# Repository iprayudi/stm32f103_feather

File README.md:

# stm32f103_feather
 Feather-compatible STM32F103 development board

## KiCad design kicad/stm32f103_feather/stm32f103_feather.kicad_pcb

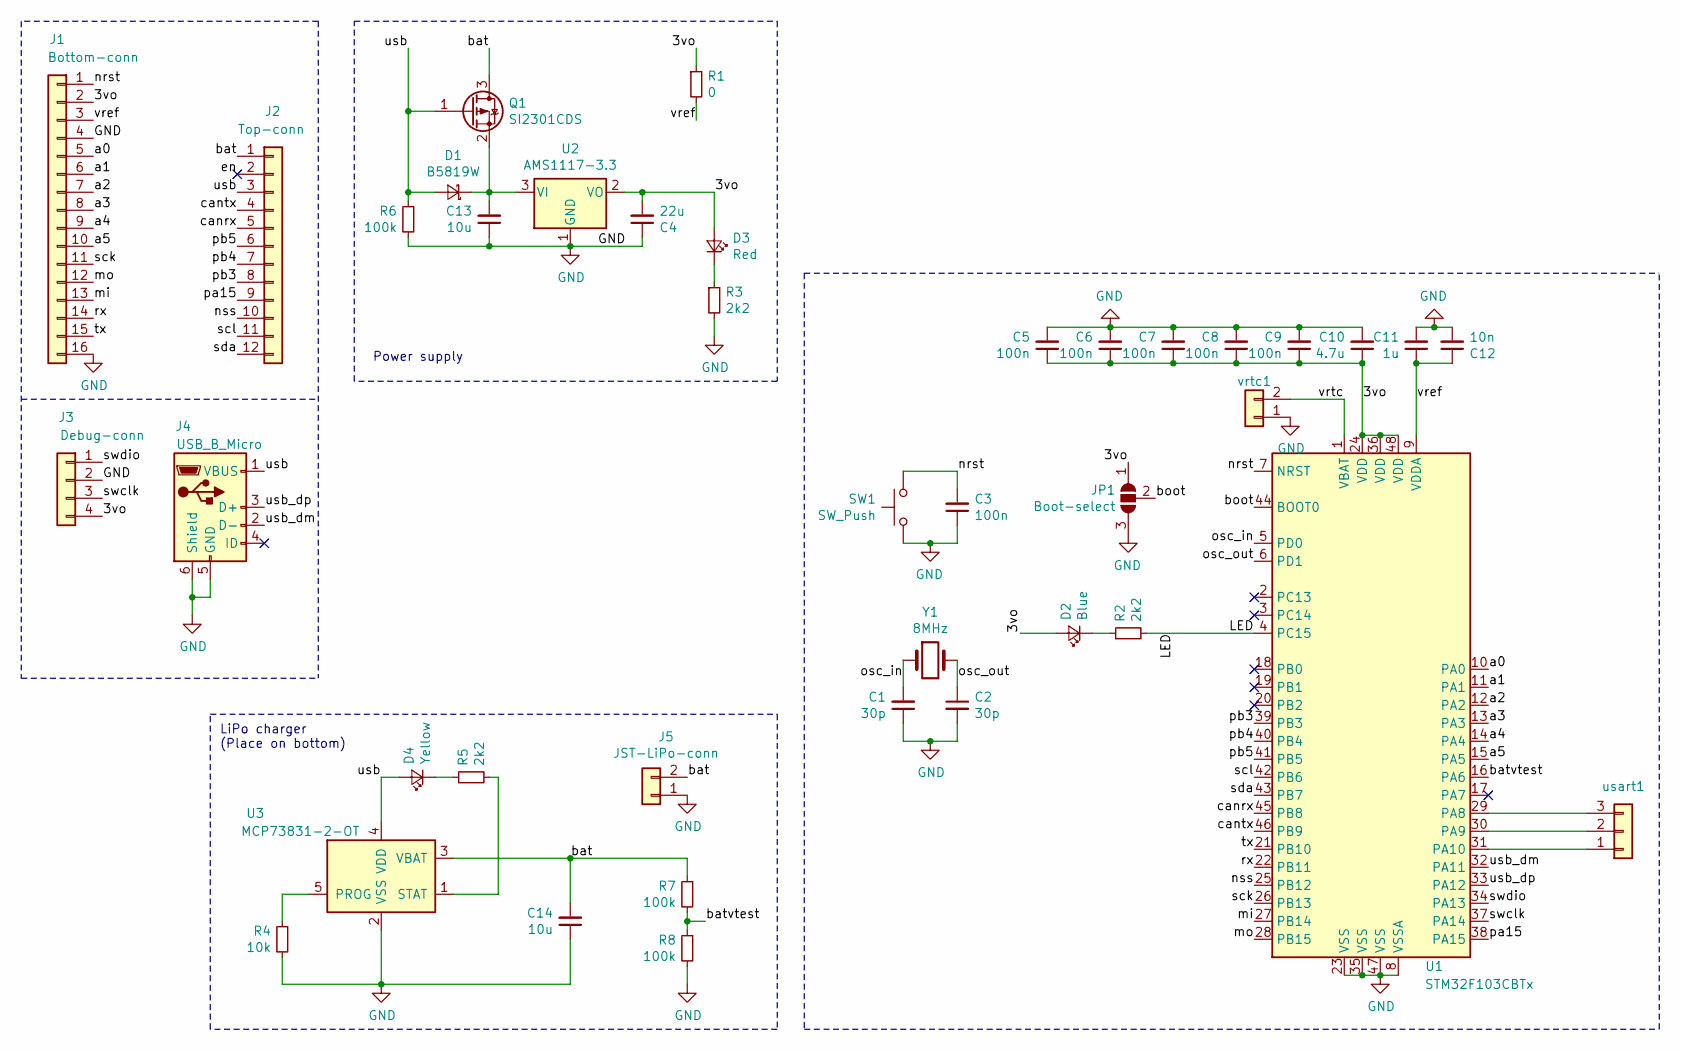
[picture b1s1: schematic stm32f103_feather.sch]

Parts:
C1, C2: 30p; C_0603_1608Metric_Pad1.05x0.95mm_HandSolder; LCSC C22397
C3, C5, C6, C7, C8, C9: 100n; C_0603_1608Metric_Pad1.05x0.95mm_HandSolder; LCSC C14663
C4: 22u; C_0603_1608Metric_Pad1.05x0.95mm_HandSolder; LCSC C59461
C10: 4.7u; C_0603_1608Metric_Pad1.05x0.95mm_HandSolder; LCSC C19666
C11: 1u; C_0805_2012Metric_Pad1.15x1.40mm_HandSolder; LCSC C15849
C12: 10n; C_0805_2012Metric_Pad1.15x1.40mm_HandSolder; LCSC C57112
C13: 10u; C_0603_1608Metric_Pad1.05x0.95mm_HandSolder; LCSC C19702
C14: 10u; C_0805_2012Metric_Pad1.15x1.40mm_HandSolder; LCSC C19702
D1: B5819W; D_SOD-123; LCSC C8598
D2: Blue; D_0603_1608Metric_Pad1.05x0.95mm_HandSolder; LCSC C72041
D3: Red; D_0603_1608Metric_Pad1.05x0.95mm_HandSolder; LCSC C2286
D4: Yellow; D_0805_2012Metric_Pad1.15x1.40mm_HandSolder; LCSC C72038
J1: Bottom-conn; PinSocket_1x16_P2.54mm_Vertical
J2: Top-conn; PinSocket_1x12_P2.54mm_Vertical
J3: Debug-conn; PinHeader_1x04_P2.54mm_Vertical
J4: USB_B_Micro; USB_Micro-B_Wuerth_629105150521
J5: JST-LiPo-conn; JST_PH_S2B-PH-SM4-TB_1x02-1MP_P2.00mm_Horizontal
JP1: Boot-select; PinHeader_1x03_P2.54mm_Vertical
Q1: SI2301CDS; SOT-23; LCSC C10487
R1: 0; R_0603_1608Metric_Pad1.05x0.95mm_HandSolder; LCSC C21189
R2, R3: 2k2; R_0603_1608Metric_Pad1.05x0.95mm_HandSolder; LCSC C4190
R4: 10k; R_0805_2012Metric_Pad1.15x1.40mm_HandSolder; LCSC C25804
R5: 2k2; R_0805_2012Metric_Pad1.15x1.40mm_HandSolder; LCSC C4190
R6: 100k; R_0603_1608Metric_Pad1.05x0.95mm_HandSolder; LCSC C25803
R7, R8: 100k; R_0805_2012Metric_Pad1.15x1.40mm_HandSolder; LCSC C25804
SW1: SW_Push; SW_SPST_TL3342; LCSC C318884
U1: STM32F103CBTx; LQFP-48_7x7mm_P0.5mm
U2: AMS1117-3.3; SOT-223-3_TabPin2; LCSC C6186
U3: MCP73831-2-OT; SOT-23-5
Y1: 8MHz; Crystal_SMD_5032-2Pin_5.0x3.2mm_HandSoldering; LCSC C115962
usart1: Conn_01x03; SolderJumper-3_P1.3mm_Open_Pad1.0x1.5mm
vrtc1: vrtc; R_0402_1005Metric

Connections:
/3vo: C4.2, C5.1, C6.1, C7.1, C8.1, C9.1, C10.1, D2.2 (A), D3.2 (A), J1.2, J3.4, JP1.1 (A), R1.1, U1.24 (VDD), U1.36 (VDD), U1.48 (VDD), U2.2 (VO)
/LED: R2.2, U1.4 (PC15)
/a0: J1.5, U1.10 (PA0)
/a1: J1.6, U1.11 (PA1)
/a2: J1.7, U1.12 (PA2)
/a3: J1.8, U1.13 (PA3)
/a4: J1.9, U1.14 (PA4)
/a5: J1.10, U1.15 (PA5)
/bat: C14.2, J2.1, J5.2, Q1.3 (D), R7.1, U3.3 (VBAT)
/batvtest: R7.2, R8.1, U1.16 (PA6)
/boot: JP1.2 (C), U1.44 (BOOT0)
/canrx: J2.5, U1.45 (PB8)
/cantx: J2.4, U1.46 (PB9)
/en: J2.2
/mi: J1.13, U1.27 (PB14)
/mo: J1.12, U1.28 (PB15)
/nrst: C3.2, J1.1, SW1.2, U1.7 (NRST)
/nss: J2.10, U1.25 (PB12)
/osc_in: C1.2, U1.5 (PD0), Y1.1
/osc_out: C2.1, U1.6 (PD1), Y1.2
/pa15: J2.9, U1.38 (PA15)
/pb3: J2.8, U1.39 (PB3)
/pb4: J2.7, U1.40 (PB4)
/pb5: J2.6, U1.41 (PB5)
/rx: J1.14, U1.22 (PB11)
/sck: J1.11, U1.26 (PB13)
/scl: J2.11, U1.42 (PB6)
/sda: J2.12, U1.43 (PB7)
/swclk: J3.3, U1.37 (PA14)
/swdio: J3.1, U1.34 (PA13)
/tx: J1.15, U1.21 (PB10)
/usb: D1.2 (A), D4.2 (A), J2.3, J4.1 (VBUS), Q1.1 (G), R6.1, U3.4 (VDD); also elsewhere on the board
/usb_dm: J4.2 (D-), U1.32 (PA11); also elsewhere on the board
/usb_dp: J4.3 (D+), U1.33 (PA12); also elsewhere on the board
/vref: C11.1, C12.1, J1.3, R1.2, U1.9 (VDDA)
/vrtc: U1.1 (VBAT), vrtc1.2
GND: C1.1, C2.2, C3.1, C4.1, C5.2, C6.2, C7.2, C8.2, C9.2, C10.2, C11.2, C12.2, C13.1, C14.1, J1.4, J1.16, J3.2, J4.5 (GND), J4.6 (Shield), J5.1, JP1.3 (B), R3.2, R4.2, R6.2, R8.2, SW1.1, U1.8 (VSSA), U1.23 (VSS), U1.35 (VSS), U1.47 (VSS), U2.1 (GND), U3.2 (VSS), vrtc1.1; also elsewhere on the board
unnamed: C13.2, D1.1 (K), Q1.2 (S), U2.3 (VI)
unnamed: D2.1 (K), R2.1
unnamed: D3.1 (K), R3.1
unnamed: D4.1 (K), R5.1
unnamed: R4.1, U3.5 (PROG)
unnamed: R5.2, U3.1 (STAT)
unnamed: U1.29 (PA8), usart1.3
unnamed: U1.30 (PA9), usart1.2
unnamed: U1.31 (PA10), usart1.1

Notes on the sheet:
LiPo charger (Place on bottom)
Power supply

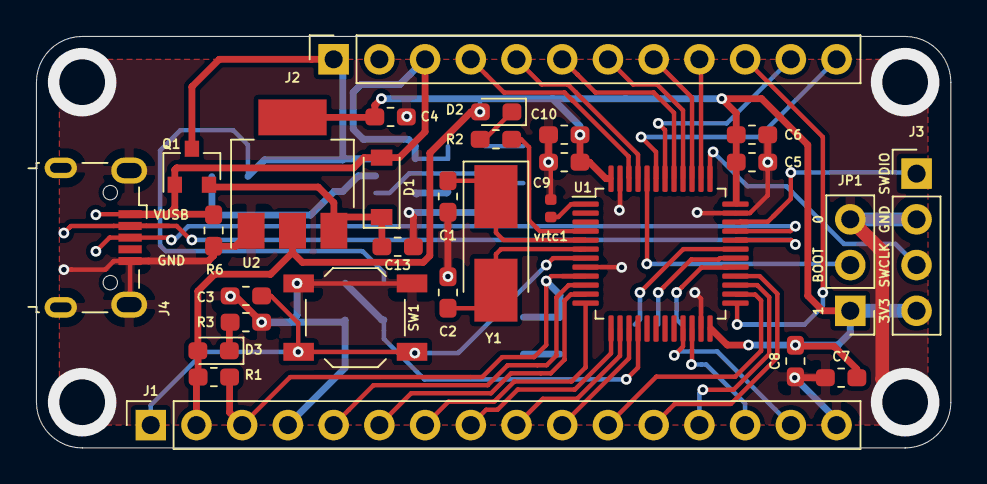
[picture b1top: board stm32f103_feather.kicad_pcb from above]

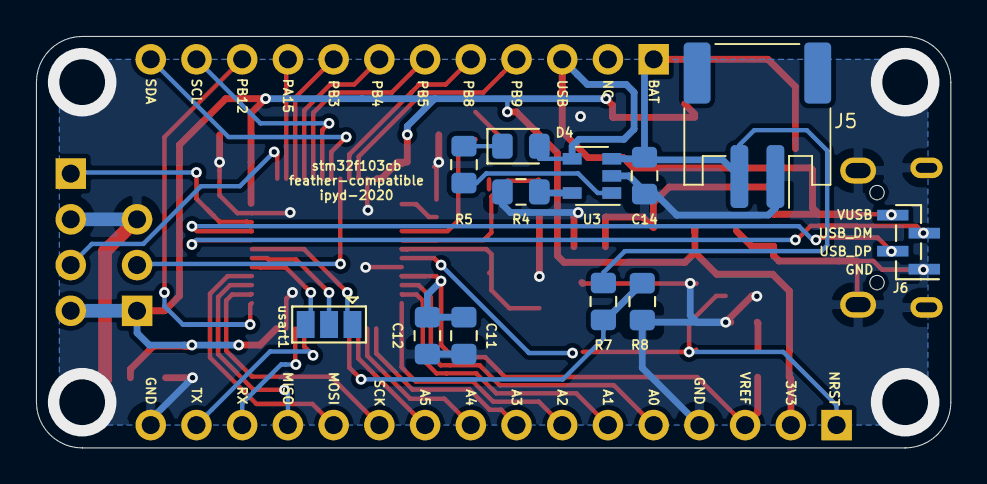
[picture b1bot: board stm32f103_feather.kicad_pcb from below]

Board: 2 copper layers, 50.8 x 22.9 mm, 41 parts (12 on the bottom side), 45 nets.

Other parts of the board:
J6: Conn_01x04; PinHeader_1x04_P1.00mm_Vertical_SMD_Pin1Left

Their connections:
/usb: J6.4; also elsewhere on the board
/usb_dm: J6.3; also elsewhere on the board
/usb_dp: J6.2; also elsewhere on the board
GND: J6.1; also elsewhere on the board

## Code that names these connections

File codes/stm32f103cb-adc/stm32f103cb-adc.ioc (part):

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Mcu.Name=STM32F103C(8-B)Tx
Mcu.Package=LQFP48
Mcu.UserName=STM32F103CBTx
PA0-WKUP.Signal=ADCx_IN0
PA13.Mode=Serial_Wire
PA13.Signal=SYS_JTMS-SWDIO
PA14.Mode=Serial_Wire
PA14.Signal=SYS_JTCK-SWCLK
PB6.Mode=I2C
PB6.Signal=I2C1_SCL
PB7.Mode=I2C
PB7.Signal=I2C1_SDA
PC15-OSC32_OUT.GPIOParameters=GPIO_Label
PC15-OSC32_OUT.GPIO_Label=LED
PC15-OSC32_OUT.Signal=GPIO_Output
RCC.SYSCLKFreq_VALUE=36000000
RCC.SYSCLKSource=RCC_SYSCLKSOURCE_PLLCLK
board=custom

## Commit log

2020-08-17 daily updates
2020-08-18 daily update
2020-09-06 example codes added
2020-09-10 added example code: counter
2020-09-11 updated codes
